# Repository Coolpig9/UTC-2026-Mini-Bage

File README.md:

# UTC-2026-Mini-Bage

This year, it was my responsibility to make our student section Mini Badges. We decided to do two badges this year:
the (Complex Airplane) as well as the [simple Airplane](#simple-airplane)

# Complex Airplane

## Kit Contents

Each kit should contain:

* 1x ATtiny85 (we used ATtiny85-20PU)
* 1x Green 3mm LED
* 1x White 3mm LED
* 2x Red   3mm LED
* 3x 2-pin SPST Buttons
* 1x 1P2T 2 Position switch (3 pins)
* 2x 750-ohm resistors
* 1x 350-ohms resistor 
* 1x BAT-HLD-003-SMT
* 1x CR2032 coin battery
* 1x Pin and Back
* 1x Complex Airplane PCP

## Assembly instructions

The key to doing this one right is taking it slow, 
you want to solder it one side at a time (back then front),
soldering the parts in reverse order of height:

Solder Order

    Back:
        1. resistors
        2. ATtiny chip
        3. battery Back
        4. switch
        5. Pin (do this one BEFORE soldering front side)

    Front: (Side with Airplane)
        1. buttons
        2. LEDs

## Example Pictures

## Complex Airplane Software Explanation

Here is the official unreleased Instruction booklet. The original plan was to print these and hand them out, but that didn't end up happening. 
[Instruction Booklet](./complexAirplaneInstructions.pdf)

Here too is a flowchart version that may help clarify things!

# Simple Airplane

## Kit Contents

Each kit should contain:

* 1x Green 3mm LED
* 1x White 3mm LED
* 2x Red   3mm LED
* 1x 1P2T 2 Position switch (3 pins)
* 1x BAT-HLD-003-SMT
* 1x CR2032 coin battery
* 1x Pin and Back
* Simple Airplane PCB

## Assembly instructions

## Example Pictures

# Would you like to remake one of these badges?

Perfect! All the stuff you need to recreate these kits is located in this repo!

## Complex
    
## Simple

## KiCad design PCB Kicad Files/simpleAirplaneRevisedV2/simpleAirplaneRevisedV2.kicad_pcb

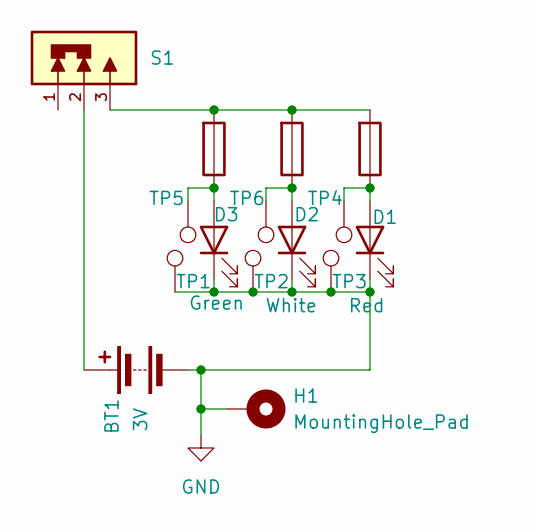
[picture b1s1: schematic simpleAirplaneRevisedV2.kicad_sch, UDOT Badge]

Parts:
BT1: 3V; BAT_BAT-HLD-003-SMT
D1: Red; LED_D3.0mm
D2: White; LED_D3.0mm
D3: Green; LED_D3.0mm
H1: MountingHole_Pad; MountingHole_2.2mm_M2_DIN965_Pad
JIC-R1, JIC-R2, JIC-R3: 0; justInCaseResistor
S1: SW_EG1218
TP1, TP2, TP3, TP4, TP5, TP6: TestPoint; TestPoint_Pad_1.0x1.0mm

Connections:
GND: BT1.2 (-), D1.1 (K), D2.1 (K), D3.1 (K), H1.1 (1_1), TP1.1 (1_1), TP2.1 (1_1), TP3.1 (1_1)
unnamed: BT1.1 (+), S1.2
unnamed: D1.2 (A), JIC-R3.2, TP4.1 (1_1)
unnamed: D2.2 (A), JIC-R2.2, TP6.1 (1_1)
unnamed: D3.2 (A), JIC-R1.2, TP5.1 (1_1)
unnamed: JIC-R1.1, JIC-R2.1, JIC-R3.1, S1.3

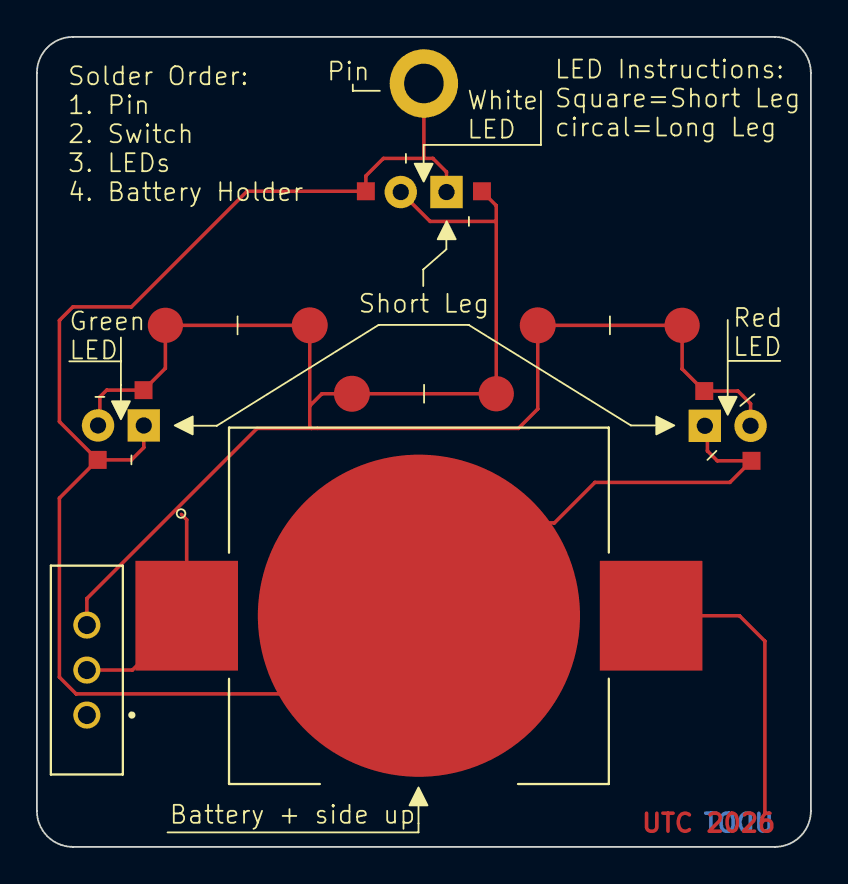
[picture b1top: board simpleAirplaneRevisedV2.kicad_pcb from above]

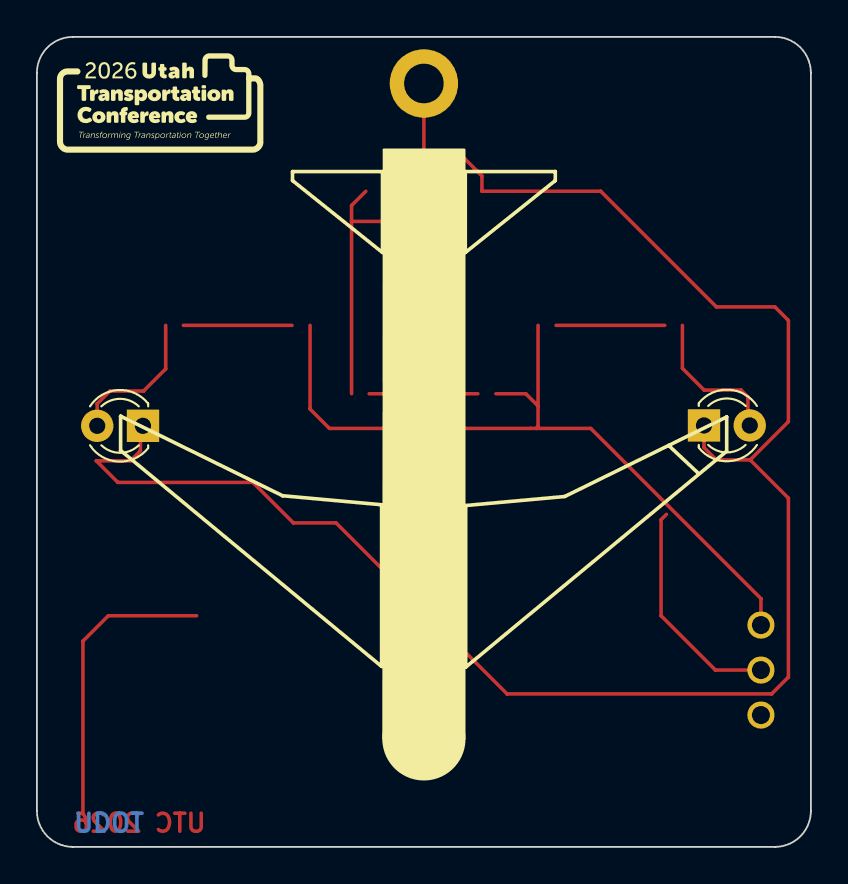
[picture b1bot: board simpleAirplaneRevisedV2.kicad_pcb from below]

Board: 2 copper layers, 43.0 x 45.0 mm, 15 parts (3 on the bottom side), 6 nets.

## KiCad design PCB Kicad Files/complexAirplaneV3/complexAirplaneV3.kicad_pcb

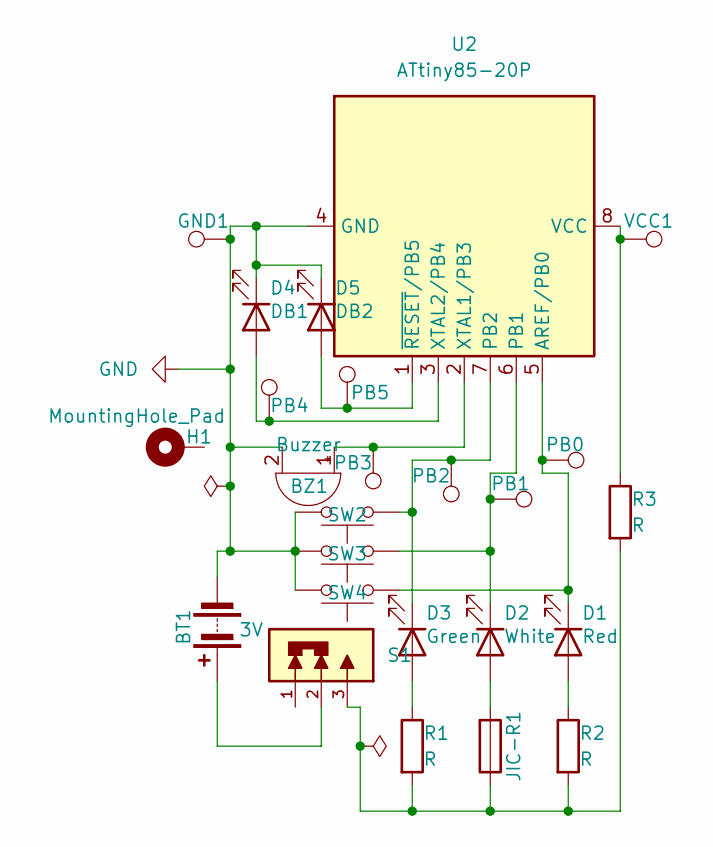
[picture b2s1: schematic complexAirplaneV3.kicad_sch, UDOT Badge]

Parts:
BT1: 3V; BAT_BAT-HLD-003-SMT
BZ1: Buzzer; PS1440P02BT_TDK -buzzer new
D1: Red; LED_D3.0mm
D2: White; LED_D3.0mm
D3: Green; LED_D3.0mm
D4: DB1; LED_D3.0mm
D5: DB2; LED_D3.0mm
GND1: TestPoint; TestPoint_Pad_1.0x1.0mm
H1: MountingHole_Pad; MountingHole_2.2mm_M2_DIN965_Pad
JIC-R1: 0; justInCaseResistor
PB0, PB1, PB2, PB3, PB4, PB5: TestPoint; TestPoint_Pad_1.0x1.0mm
R1, R2, R3: R; R_Axial_DIN0207_L6.3mm_D2.5mm_P7.62mm_Horizontal
S1: SW_EG1218
SW2, SW3, SW4: SW_Push; button-SW_SWT0330-050016TSG_REVA
U2: ATtiny85-20P; DIP-8_W7.62mm
VCC1: TestPoint; TestPoint_Pad_1.0x1.0mm

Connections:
GND: BT1.2 (-), BZ1.2 (-), D4.1 (K), D5.1 (K), GND1.1 (1_1), SW2.2, SW3.2, SW4.2, U2.4 (GND)
unnamed: BT1.1 (+), S1.2
unnamed: BZ1.1 (+), PB3.1 (1_1), U2.2 (XTAL1/PB3)
unnamed: D1.2 (A), R2.1
unnamed: D1.1 (K), PB0.1 (1_1), SW4.1, U2.5 (AREF/PB0)
unnamed: D2.2 (A), JIC-R1.1
unnamed: D2.1 (K), PB1.1 (1_1), SW3.1, U2.6 (PB1)
unnamed: D3.2 (A), R1.1
unnamed: D3.1 (K), PB2.1 (1_1), SW2.1, U2.7 (PB2)
unnamed: D4.2 (A), PB4.1 (1_1), U2.3 (XTAL2/PB4)
unnamed: D5.2 (A), PB5.1 (1_1), U2.1 (~RESET/PB5)
unnamed: JIC-R1.2, R1.2, R2.2, R3.2, S1.3
unnamed: R3.1, U2.8 (VCC), VCC1.1 (1_1)

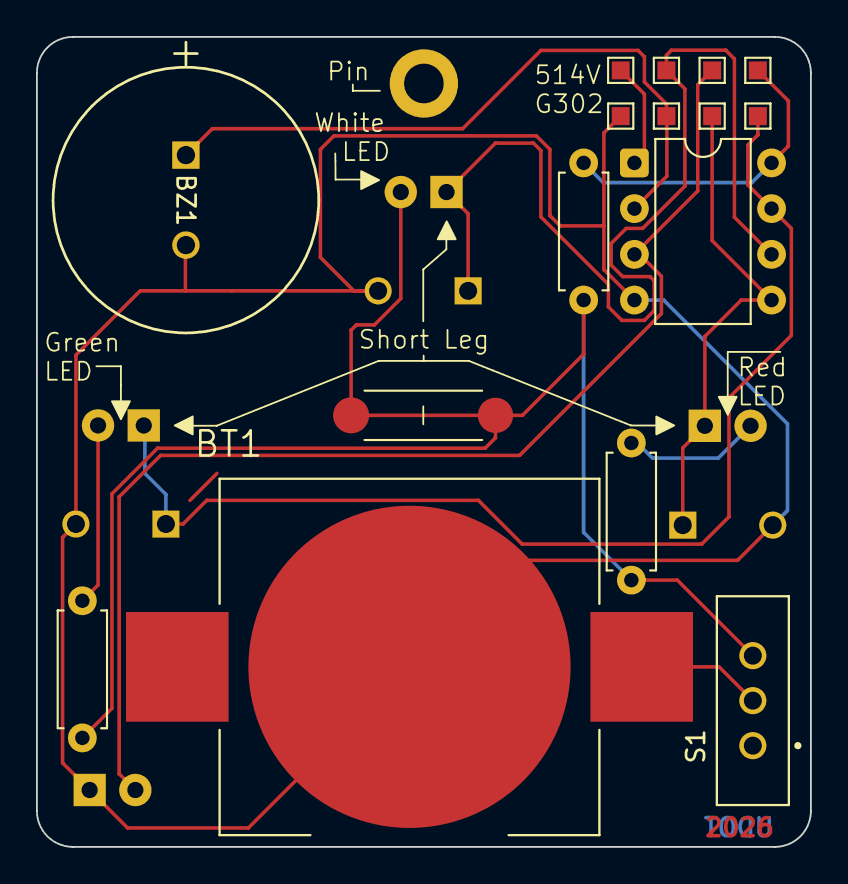
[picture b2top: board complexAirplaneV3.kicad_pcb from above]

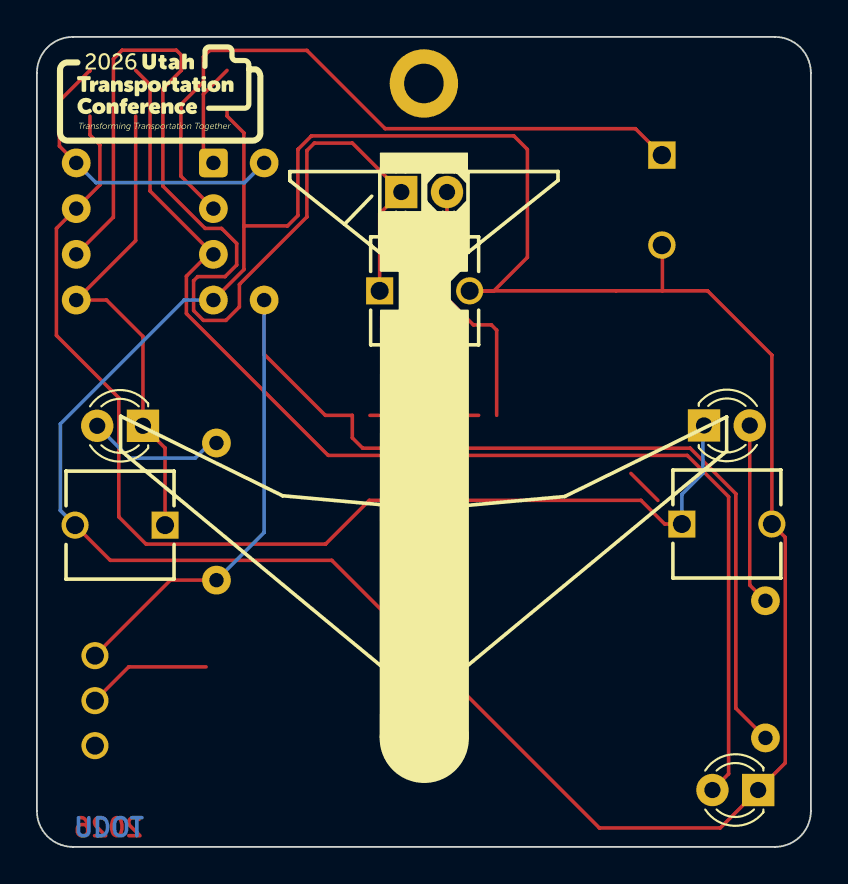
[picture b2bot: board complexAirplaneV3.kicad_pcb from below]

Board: 2 copper layers, 43.0 x 45.0 mm, 24 parts (7 on the bottom side), 13 nets.
